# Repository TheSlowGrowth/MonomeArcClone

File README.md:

# Monome Arc Clone

An open source, protocol-compatible clone of the monome arc.

## Before you start

Please note: if you encounter a problem, please **do not post on the
monome forums**! Tehn will surely help you, but I don’t want my clone
to cause them trouble and work. I’m very happy that they make their
protocols open and I would like them to continue to do so in the spirit
of openness.

For assistance, please write an email to my address instead:
<mail@johannesneumann.net> I will try to help you out.

## Required tools

During assembly and setup you will need the following tools

-   AVR ISP programming device (supported by avrdude). I recommend
    [USBasp](http://www.fischl.de/usbasp/) or any of its clones.
    Alternatively you can also use STK500v2 clones or any other
    programmer that supports the ISP protocol. You get something like
    this on ebay for under 20€.
-   Soldering iron, decent(!) flux, tweezers, solder wick
-   a computer capable of flashing AVRs and FTDI EEPROMs
-   a multimeter

## Software installation

Before you start, please install all the software that’s needed to run monome devices. Please look at the instructions provided by [http://monome.org](http://monome.org/). Even though you might not have a functioning monome at this point, we will need the drivers during the setup process.

Install the drivers for your AVR ISP programmer, if you haven’t already.

### Windows

Install *WINAVR* from [this link](http://www.webring.org/l/rd?ring=avr;id=59;url=http://winavr.sourceforge.net/). This will install a AVR compiler and (more important) a tool called *avrdude* to upload the software to the ATMega88p microprocessor used in the device.

Install *AVR-Burn-O-Mat* from [this link](http://avr8-burn-o-mat.aaabbb.de/). This little tool will make it easier to upload the software to the chip as it provides a nice graphical user interface to *avrdude* installed with WINAVR.

Now we need to edit some files. Unfortunately as I am writing this (05.11.2014) it seems that some versions of *avrdude* and *AVR-Burn-O-Mat* don’t know the ATMega88p processor yet. So we teach them that it exists.

First, go to C:\\WINAVR\...\....\\bin\\avrdude.conf and open it with a text editor (I recommend geany).

Search for "ATMega88p". If it takes you to something like this:

```
#------------------------------------------------------------

# Atmega88p

#------------------------------------------------------------
```

…then you don’t have to edit anything and the file is fine. Simply go to the next step.

If nothing is found, search for this part:

```
#------------------------------------------------------------

# ATmega88

#------------------------------------------------------------
```

This is the header for the (almost) equal ATMega88. We simply copy the whole passage below this line (down to the next similar looking header) and change a few things. The whole passage you have to copy is roughly 200 lines long.

Duplicate the whole passage and change the beginning to:

```
#------------------------------------------------------------

# ATmega88p

#------------------------------------------------------------

part

id = "m88p";

desc = "ATMEGA88P";

has_debugwire = yes;

flash_instr = 0xB6, 0x01, 0x11;

eeprom_instr = 0xBD, 0xF2, 0xBD, 0xE1, 0xBB, 0xCF, 0xB4, 0x00,

0xBE, 0x01, 0xB6, 0x01, 0xBC, 0x00, 0xBB, 0xBF,

0x99, 0xF9, 0xBB, 0xAF;

stk500_devcode = 0x73;

# avr910_devcode = 0x;

signature = 0x1e 0x93 0x0f;

pagel = 0xd7;

bs2 = 0xc2;

...

... more stuff follows here ...

...
```

Now avrdude knows the microprocessor.

Now we have to teach *AVR-Burn-O-Mat* as well. Go to the installation directory (mine is: `D:\Program Files (x86)\AVR Burn-O-Mat)` and open the file `AVR8_Burn_O_Mat_Config.xml`. With a text editor (e.g. geany).

Again, search for "Atmega88p". If it can be found, all is well and you don't have to do anything here. If nothing is found, search for "Atmega88". It should take you to this line:

```
<AVR name="m88" caption="ATmega88">
   <Fuse name="UNUSED_E7" bit="7" ...

```
Copy the whole block (everything between `<AVR name="m88" ... ` and `</AVR>`) and change the first line to 
```
<AVR name="m88p" caption="ATmega88p">
```
Now *AVR-Burn-O-Mat* can program your Atmega88p processor.

Now open *AVR-Burn-O-Mat* and go to the settings page. Check if the directories are correct and enter the connection settings for your programmer.

I’m using an STK500V2 clone here, but if you click the dropdown menu, it will give you other options, such as USBasp. For most USB programmers, the Port must be set to "usb" or (if they are based on a serial COM interface) the respective COM port. You can open the device manager and plug in your programmer, then it should display the COM port in brackets behind the device name.

Install FT-Prog from [this website](http://www.ftdichip.com/Support/Utilities.htm). We will need it to configure the FTDI USB chip on the board.

### Linux

On Linux, install avrdude using your system’s package manager.

Compile libftdi with the confuse library already present, and make sure you can run the ftdi_eeprom command it comes with. This is currently untested on linux, please refer to [this guide](https://waterpigs.co.uk/articles/ftdi-configure-mac-linux/) for pointers on how to do it.

### Mac OS X

Install avrdude, and avr-gcc if you want to compile your own hex files. You can do this either manually, or via [CrossPack](https://obdev.at/products/crosspack/download.html).

In order to be able to flash the FTDI chip’s EEPROM, you’ll need to install libftdi with the confuse library already installed. This is possible either manually, or using homebrew with a change to the libftdi formula detailed [here](https://waterpigs.co.uk/articles/ftdi-configure-mac-linux/).

Some old versions of CrossPack will be missing the avrdude reference files for the ATMega88p. You can test this by running `avrdude -c stk500v2 -p m88p`. If you get `avrdude: AVR Part "88p" not found.` then follow the instructions in the Windows section above, duplicating the ATMega88 definition for the 88p. Look for an avrdude.conf file to make these changes in, e.g. `/usr/local/CrossPack-AVR-20100115/etc/avrdude.conf`

## USB Board Assembly

I won’t give step-by-step instructions for soldering. If you are not familiar with soldering and electronics in general, please do an easier project first. It can become very frustrating otherwise.

Once you’re done assembling the USB board, go to the device manager (Windows) or USB Prober (Mac OS). Connect the USB board to your computer via the USB jack and install the BUS\_PWRD jumper on the USB board. You should see the device manager refresh and a new COM port device will appear.

If it does not appear, please disconnect it immediately and check your soldering!

Now we have to check the voltage of the on-board regulator. Connect a multimeter to the pins highlighted in the following picture:

Your meter should read 3,6V (or thereabouts). Fine, it looks like everything is okay.

Lets go on and flash the firmware to the chip. Connect your programmer to the 10-pin connector on the USB board. This connector is not the one commonly used for AVR devices, but it uses the same pinout and attaches to the same type of cables. You can simply use your programmers 10-pin cable and crimp micromatch connector to it. This should now be plugged into the USB board. Check the orientation. A good help can be the four ground-pins, which are connected to each other. On both the USB board and the programmer. Pin 1 of the cable is on the opposite side. In the image above, it is the pin on the bottom right of the connector, next to the "R14" label.

Also be sure, that the USB board is plugged into your computer as well and the BUS\_PWRD jumper is installed, so the processor receives power.

### Windows (AVR-Burn-O-Mat + FT_PROG)

Open *AVR-Burn-O-Mat *and connect your programmer to your PC.

First, we need to change the fuse-bits in the processor, to use the external 20MHz crystal as a clock source. Select Atmega88p from the "AVR type" menu. Then click on "Fuses"

In the new window, click "read fuses".

You should see some commands run in the bottom of the main window and eventually a message will pop up, saying: "fuses successfully read". If not: Check the commands in the main window. They can give you a hint to where the problem is. Usually the programmer settings are wrong (wrong COM port\...) or the USB board is not connected properly. Some programmers offer a "low speed" programming mode, this should be used, as the processor is currently still running at its internal low clock speed.

If verything is fine, we can edit the fuse-bits to use the external crystal. Click on the "Oscillator/Clock Options" tab, then un-tick "divide system clock by 8" and select the "Full swing crystal oscillator" tab.

Double check everything! You might screw your chip up! Never attempt to write the fuses, if you were not able to correctly read them before. You might end up with a chip that has its programming interface disabled and can’t be rescued even with professional equipment.

Okay, once you are sure, everything is correct and matches the image below, you can click "write fuses" and again, some commands should run in the main window and a message should say: "Fuses successfully written". Then click "read fuses" again. If they can be read successfully, you have done everything right.

Now we can flash the firmware. Close the fuses window and select the firmware file in the main window. I recommend to use the pre-compiled one in the repository. I want to build an arc 4 here, so I chose the matching firmware. Be sure to use the right file. Using another file will probably make the processor "think" its connected to some hardware which is not there. This can create short circuits and might destroy the chip. So please double check here!

Click "write" and the commands in the bottom of the window should start executing again. Eventually it will say "Flash sucessfully written."

Nice! Now you can unplug the programmer.

Now we have to configure the USB-chip on the board to be recognized by serialosc so you can use your clone just like a real monome arc.

Start FT\_PROG and connect the USB board to your computer via its USB connector. In the FT\_PROG window, click the search icon until it displays your device.

Eventually after a few retries you get this. Go to the "SerialNumber" tab and untick "Auto Generate Serial No:". Now you can edit the "serial number" field. Enter a serial number like in the image above. It should start with an "m" and the numbers after that are irrelevant, but I found that they should be 7 digits long. They represent the "unique number" of your device. If you have other monomes, be sure that you use a different serial number that the one of your other devices. Also change the manufacturer to "monome", this is important for compatibility with monome eurorack modules and the Aleph. Once you’re done, click the flash symbol and program the new settings to the chip.

### Linux/Mac OS (avrdude + libftdi ftdi_eeprom)

Connect your AVR programmer to your computer, and the USB board to the programmer. In each of the following commands, replace `YOUR_PROGRAMMER_ID` with the relevant ID (e.g. stk500v2) and `YOUR_PROGRAMMER_PORT` with the relevant port (e.g. `/dev/cu.usbmodem00177932`.

First, set the fuses, based on [this fuse calculation](http://eleccelerator.com/fusecalc/fusecalc.php?chip=atmega88p&LOW=D6&HIGH=DF&EXTENDED=F9&LOCKBIT=FF):

`avrdude -V -p m88p -c YOUR_PROGRAMMER_ID -P YOUR_PROGRAMMER_PORT -B 10 -e -u -U lfuse:w:0xD6:m -U hfuse:w:0xDF:m -U efuse:w:0xF9:m -U lock:w:0xFF:m`

Then, flash the USB board firmware. Swap `arc4_` for `arc2_` in the unlikely event you’re building a two-ring arc:

`avrdude -V -p m88p -c YOUR_PROGRAMMER_ID -P YOUR_PROGRAMMER_PORT -B 2 -U flash:w:./firmware/compiled_hex/arc4_firmware_usb_board_atmega88p.hex:i -U lock:w:0xFF:m`

To flash the FTDI EEPROM, edit `firmware/monome-arc-clone-ftdi-eeprom.conf` to have your desired serial number (which must be m followed by seven digits), then run the following command with your FTDI driver disabled:

`ftdi_eeprom --flash-eeprom firmware/monome-arc-clone-ftdi-eeprom.conf`

Don’t forget to re-enable your FTDI driver afterwards! Refer to this [libftdi guide](https://waterpigs.co.uk/articles/ftdi-configure-mac-linux/) for more information.

### Testing

Now you can open a monome app with your USB board connected, and you should see your clone appear in the device list. If it does not appear, check your serialosc settings.

## Pot board and ring board assembly

Assemble the ring boards and the pot boards. Start with one pair of them to find errors early.

At full brightness, each LED is supplied with a 3.3V square wave with 25% duty cycle, current limited to around 2.6mA (with a 9.1kohm current set resistor). Not all LEDs perform well at such low currents. Testing found the IN-S63AT5UW to be an excellent trade-off between price and performance. Prices in the comparison are from late 2018.

When soldering the surface mounted headers which connect each ring board to the encoder board, solder only one connector first, insert the other connector onto that, then temporarily screw the boards together and make a couple of solder joints to fix the other connector in exactly the right mating position. If soldered without checking the location, you risk the boards being misaligned.

Use the 8pin micromatch connectors and ribbon cables to connect the pot board to the USB board via their micromatch connectors (Not the one marked with ISP, the smaller one.) Connect the USB board to your computer and check the BUS\_PWRD jumper. The USB board should now receive power, and supply the pot board via the ribbon cable that connects the two.

Attach your AVR programmer to the board, then set the fuses and flash the firmware as with the USB Board, but using `firmware_pot_board_atmega88p.hex` rather than the USB board hex file.

Once the pot boards processor is programmed with the right fuses and firmware, you should disconnect the usb cable and set the address selection switch to off/off. This equals to address 0, which is used for the first LED ring in the monome arc clone.

Now attach the led ring.

Connect the USB board to the computer again and the led ring should light up for a short time (part of the startup animation). Open the [monome arc test app](http://docs.monome.org/lib/exe/fetch.php?media=app:monome_test_110.zip) and check everything.

Then assemble the other boards and connect them to the ribbon cable. Flash them the same way and check them with the test app. Be sure to use the right addresses:

```
  ------------- ---------- ----------
  Ring number   Switch 2   Switch 1
  0             Off        Off
  1             Off        On
  2             On         Off
  3             On         On
  ------------- ---------- ----------
```

Double check that all the boards function correctly before final assembly. Make sure that all LEDs light, that the encoders send turn and button press messages, and that the boards are in the right order.

If you don’t have Max MSP and don’t want to install the very large free Max player, you can use the small Puredata arc test patch in `firmware/arc-scratchpad.pd` to test and debug your arc. It should run in any version of Puredata, and requires no externals.

## Physical Case Construction and Assembly

Assuming you’re working with a milled panel based on `case/Alu Faceplate.pdf` and laser cut acrylic parts based on the Glas-Ring and Light_Shaper drawings, assembly is quite straightforward. The fit of the laser cut parts is tight, and often the outer diameter is slightly larger on one edge than the other, so look carefully at the edge angles of both parts and experiment with their orientation to find the best results. You can see the angles here:

Depending on the quality of your laser cutter, you may have to manually remove some leftover parts from the light shaper with a small sharp knife.

For a more diffused light from the LEDs, either cut the rings from frosted acyrlic, lightly sand the underside of the rings with 400 grit sandpaper, or perhaps put a ring of very thin paper between the ring and light shaper.

The blind threaded holes in the top panel are not deep enough for normal male-female M3 hex spacers, so insert 12mm setscrews (preferably fastened with thread lock e.g. loctite) and then screw 4mm female-female hex spacers over them before attaching the ring board.

The simplest case solution is to cut a 4mm acrylic backplate from `case/Acrylic Glass Back Panel 266 x 74.svg`, then assemble the boards and plates as shown (note that the given acrylic back plate has one set of mounting holes in a different location to shown here. Either cut the backplate with holes in the outside corners, or alter the assembly to suit):

You’ll need the following hardware:

* 16 x 12mm M3 Set Screw
* 16 x 4mm M3 FF hex spacer
* 10 x 12mm M3 FF hex spacer
* 4 x 4mm M3 MF hex spacer
* 6 x M3 Nut
* 6 x 6mm M3 Screw
* 4 x 8mm M3 Screw

If you want to build a more comprehensive case, refer to the layout in `case/Monome Arc Clone Walnut Case.ezdraw` and `case/Monome Arc Clone Walnut Case Plans 500 x 360.svg` for dimensions to design a case around. Make sure the bounding box in the SVG is scaled to 500mm by 360mm in your CAD application, and then everything else should be the correct size. Parts for the CNC-routed wooden case and knobs shown below are given as an example.

Congratulations on assembling your arc!

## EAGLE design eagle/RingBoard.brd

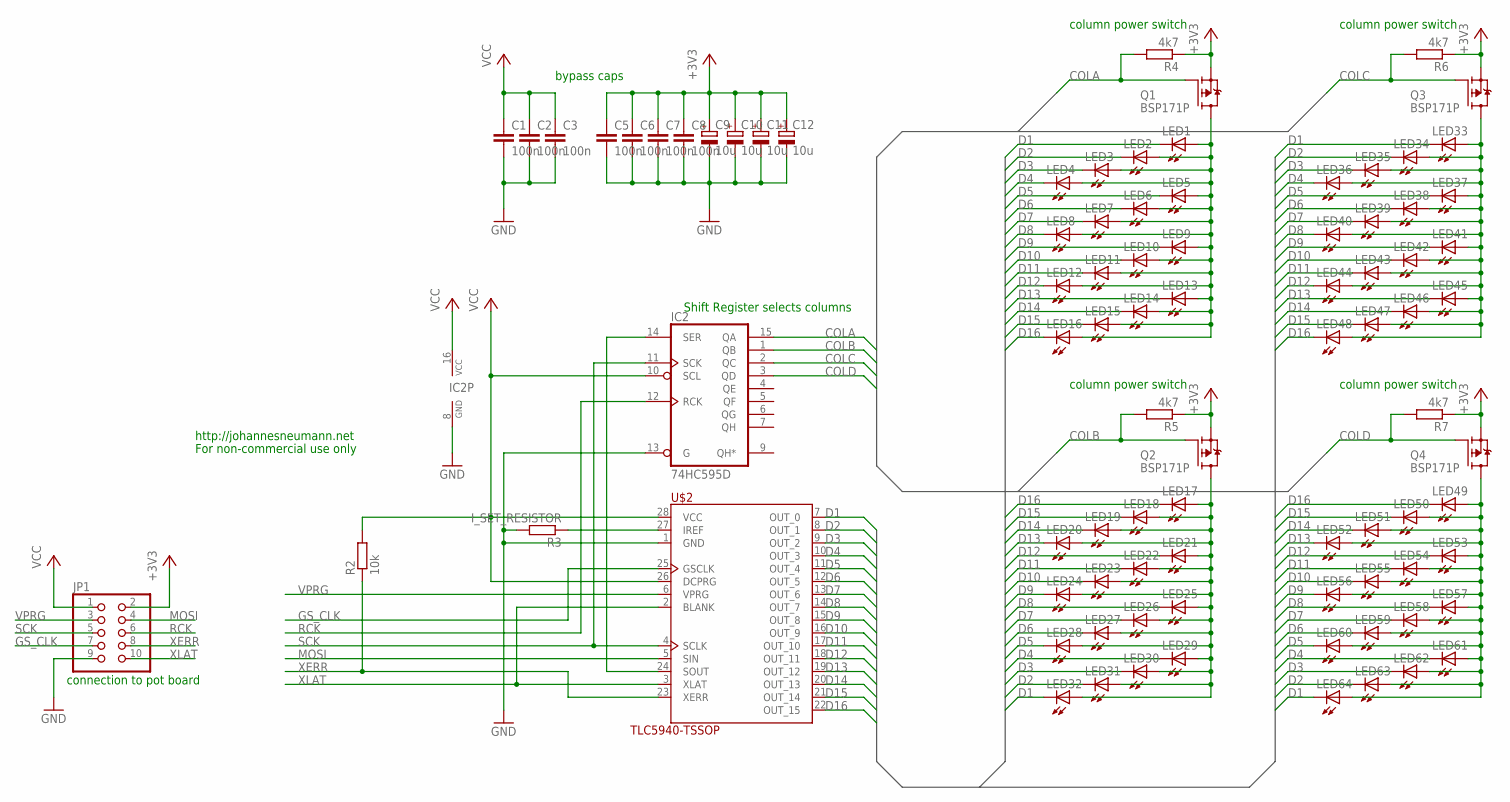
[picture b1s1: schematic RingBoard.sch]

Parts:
C1, C2, C3, C5, C6, C7, C8: 100n; C0603
C9, C10, C11, C12: 10u; 153CLV-0605
IC2: 74HC595D; SO16
JP1: PINHD-2X5_2.54-SMD; 2X05SMD
LED1, LED2, LED3, LED4, LED5, LED6, LED7, LED8, LED9, LED10, LED11, LED12, LED13, LED14, LED15, LED16, LED17, LED18, LED19, LED20, LED21, LED22, LED23, LED24, LED25, LED26, LED27, LED28, LED29, LED30, LED31, LED32, LED33, LED34, LED35, LED36, LED37, LED38, LED39, LED40, LED41, LED42, LED43, LED44, LED45, LED46, LED47, LED48, LED49, LED50, LED51, LED52, LED53, LED54, LED55, LED56, LED57, LED58, LED59, LED60, LED61, LED62, LED63, LED64: LEDCHIP-LED0805; CHIP-LED0805
Q1, Q2, Q3, Q4: BSP171P; SOT223
R2: 10k; R0603
R3: I_SET_RESISTOR; M1406
R4, R5, R6, R7: 4k7; R0603
U$2: TLC5940-TSSOP; HTSSOP-28

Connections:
+3V3: C5.1, C6.1, C7.1, C8.1, C9.+, C10.+, C11.+, C12.+, JP1.2, Q1.3 (S), Q2.3 (S), Q3.3 (S), Q4.3 (S), R4.1, R5.1, R6.1, R7.1
COLA: IC2.15 (QA), Q1.1 (G), R4.2
COLB: IC2.1 (QB), Q2.1 (G), R5.2
COLC: IC2.2 (QC), Q3.1 (G), R6.2
COLD: IC2.3 (QD), Q4.1 (G), R7.2
D1: LED1.C, LED32.C, LED33.C, LED64.C, U$2.7 (OUT_0)
D2: LED2.C, LED31.C, LED34.C, LED63.C, U$2.8 (OUT_1)
D3: LED3.C, LED30.C, LED35.C, LED62.C, U$2.9 (OUT_2)
D4: LED4.C, LED29.C, LED36.C, LED61.C, U$2.10 (OUT_3)
D5: LED5.C, LED28.C, LED37.C, LED60.C, U$2.11 (OUT_4)
D6: LED6.C, LED27.C, LED38.C, LED59.C, U$2.12 (OUT_5)
D7: LED7.C, LED26.C, LED39.C, LED58.C, U$2.13 (OUT_6)
D8: LED8.C, LED25.C, LED40.C, LED57.C, U$2.14 (OUT_7)
D9: LED9.C, LED24.C, LED41.C, LED56.C, U$2.15 (OUT_8)
D10: LED10.C, LED23.C, LED42.C, LED55.C, U$2.16 (OUT_9)
D11: LED11.C, LED22.C, LED43.C, LED54.C, U$2.17 (OUT_10)
D12: LED12.C, LED21.C, LED44.C, LED53.C, U$2.18 (OUT_11)
D13: LED13.C, LED20.C, LED45.C, LED52.C, U$2.19 (OUT_12)
D14: LED14.C, LED19.C, LED46.C, LED51.C, U$2.20 (OUT_13)
D15: LED15.C, LED18.C, LED47.C, LED50.C, U$2.21 (OUT_14)
D16: LED16.C, LED17.C, LED48.C, LED49.C, U$2.22 (OUT_15)
GND: C1.2, C2.2, C3.2, C5.2, C6.2, C7.2, C8.2, C9.-, C10.-, C11.-, C12.-, IC2.8 (GND), IC2.13 (G), JP1.9, R3.2, U$2.1 (GND)
GS_CLK: JP1.7, U$2.25 (GSCLK)
MOSI: JP1.4, U$2.5 (SIN)
unnamed: IC2.14 (SER), U$2.24 (SOUT)
unnamed: LED17.A, LED18.A, LED19.A, LED20.A, LED21.A, LED22.A, LED23.A, LED24.A, LED25.A, LED26.A, LED27.A, LED28.A, LED29.A, LED30.A, LED31.A, LED32.A, Q2.2 (D), Q2.4 (D)
unnamed: LED33.A, LED34.A, LED35.A, LED36.A, LED37.A, LED38.A, LED39.A, LED40.A, LED41.A, LED42.A, LED43.A, LED44.A, LED45.A, LED46.A, LED47.A, LED48.A, Q3.2 (D), Q3.4 (D)
unnamed: LED49.A, LED50.A, LED51.A, LED52.A, LED53.A, LED54.A, LED55.A, LED56.A, LED57.A, LED58.A, LED59.A, LED60.A, LED61.A, LED62.A, LED63.A, LED64.A, Q4.2 (D), Q4.4 (D)
unnamed: LED1.A, LED2.A, LED3.A, LED4.A, LED5.A, LED6.A, LED7.A, LED8.A, LED9.A, LED10.A, LED11.A, LED12.A, LED13.A, LED14.A, LED15.A, LED16.A, Q1.2 (D), Q1.4 (D)
unnamed: R3.1, U$2.27 (IREF)
RCK: IC2.12 (RCK), JP1.6
SCK: IC2.11 (SCK), JP1.5, U$2.4 (SCLK)
VCC: C1.1, C2.1, C3.1, IC2.10 (SCL), IC2.16 (VCC), JP1.1, R2.2, U$2.26 (DCPRG), U$2.28 (VCC)
VPRG: JP1.3, U$2.6 (VPRG)
XERR: JP1.8, R2.1, U$2.23 (XERR)
XLAT: JP1.10, U$2.2 (BLANK), U$2.3 (XLAT)

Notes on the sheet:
Shift Register selects columns
http://johannesneumann.net
For non-commercial use only
connection to pot board
column power switch
bypass caps

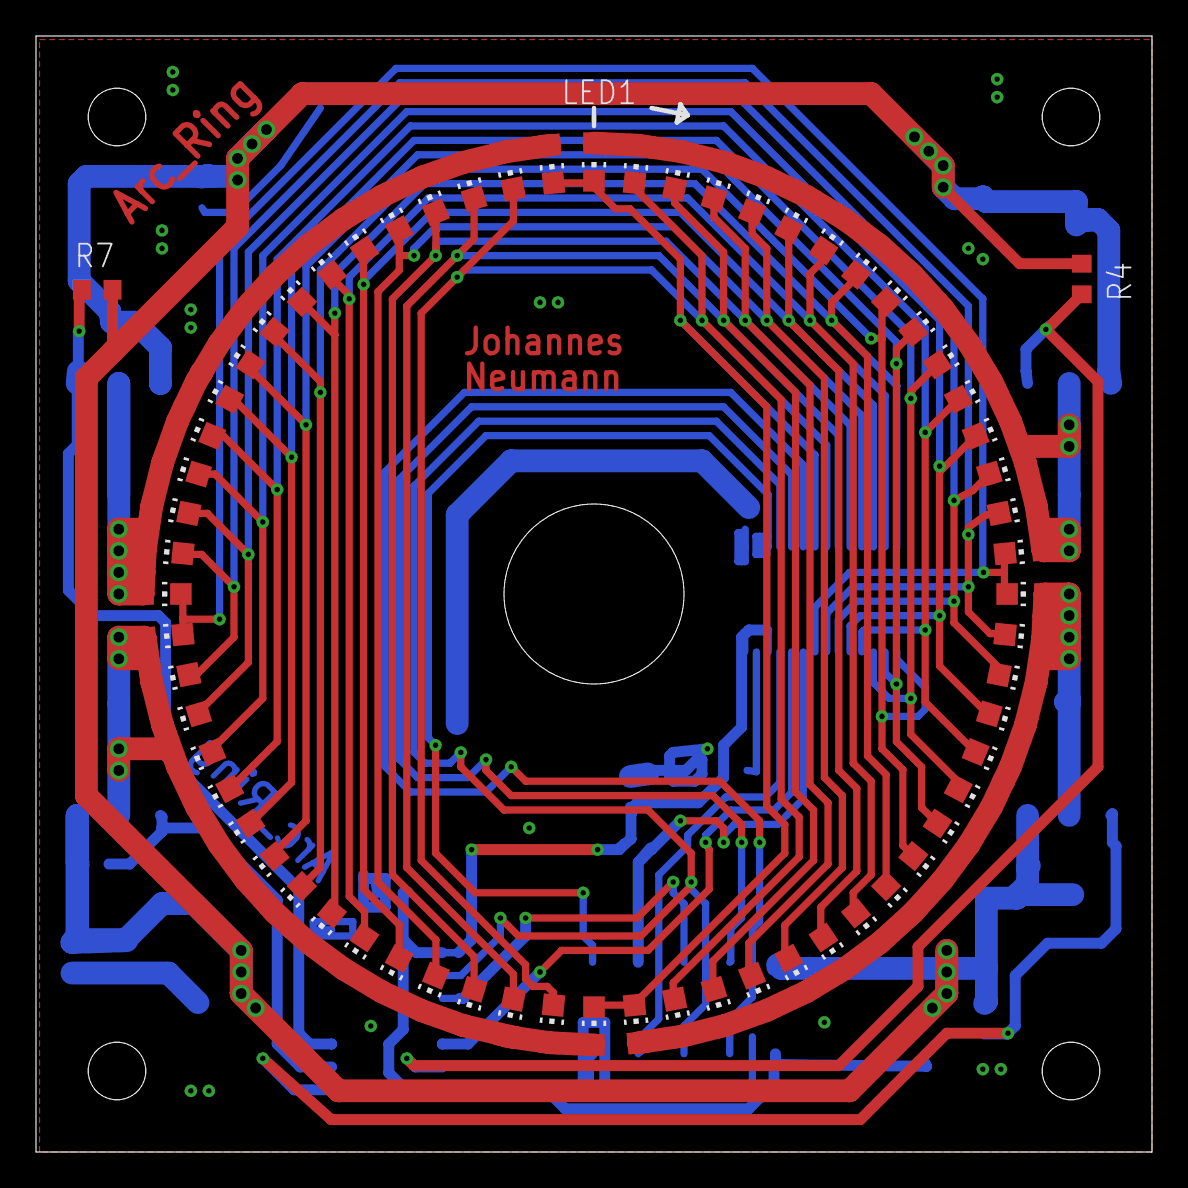
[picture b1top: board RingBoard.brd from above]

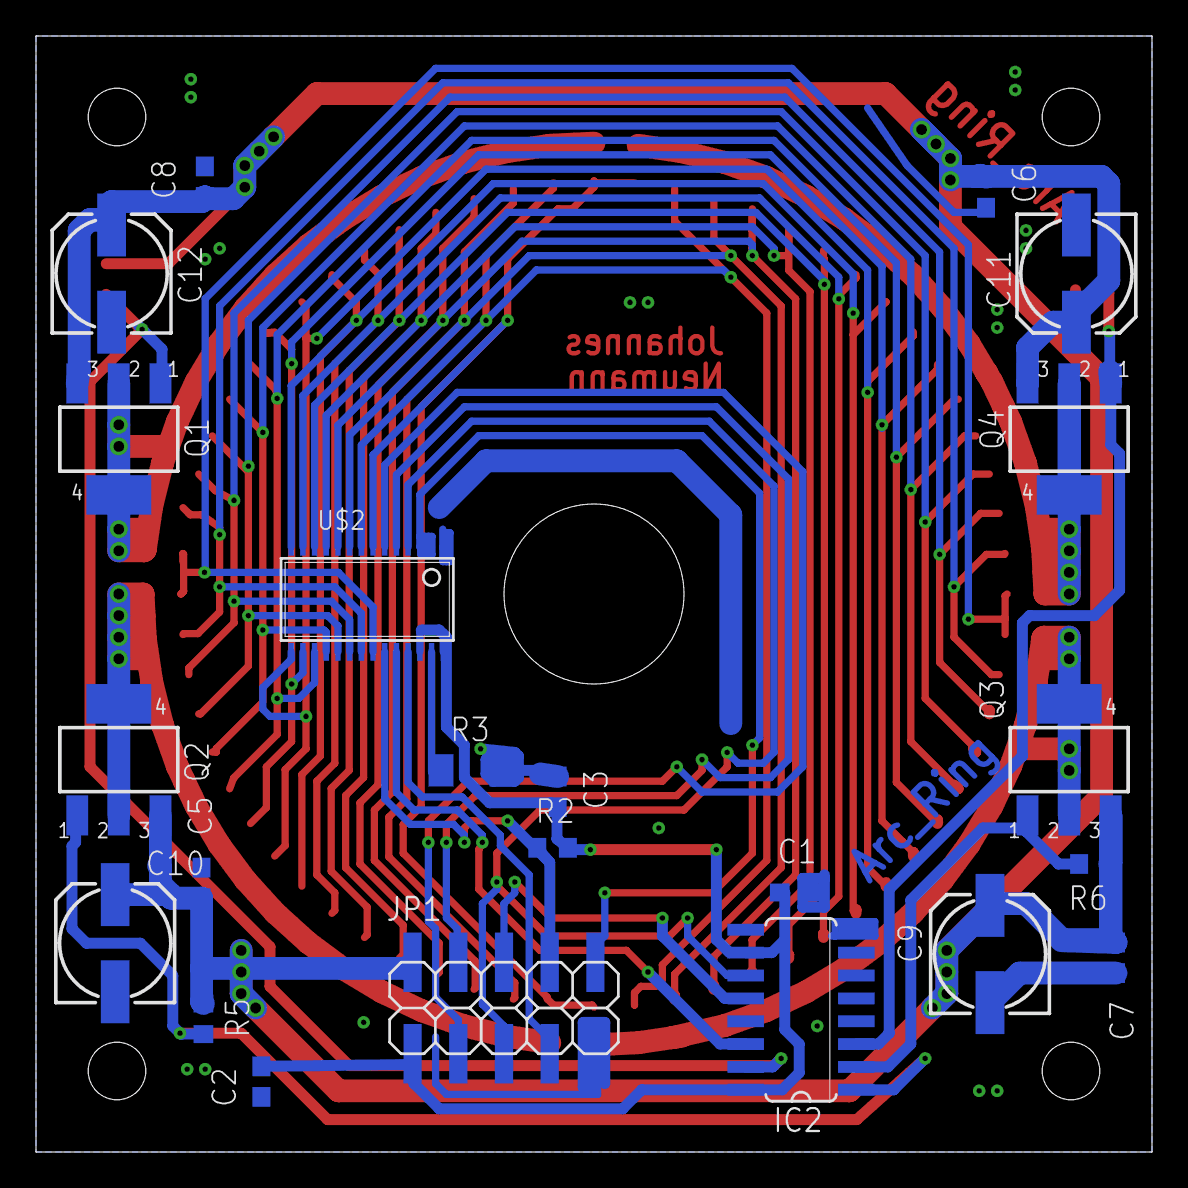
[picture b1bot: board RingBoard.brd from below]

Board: 2 copper layers, 62.0 x 62.0 mm, 88 parts (22 on the bottom side), 36 nets.

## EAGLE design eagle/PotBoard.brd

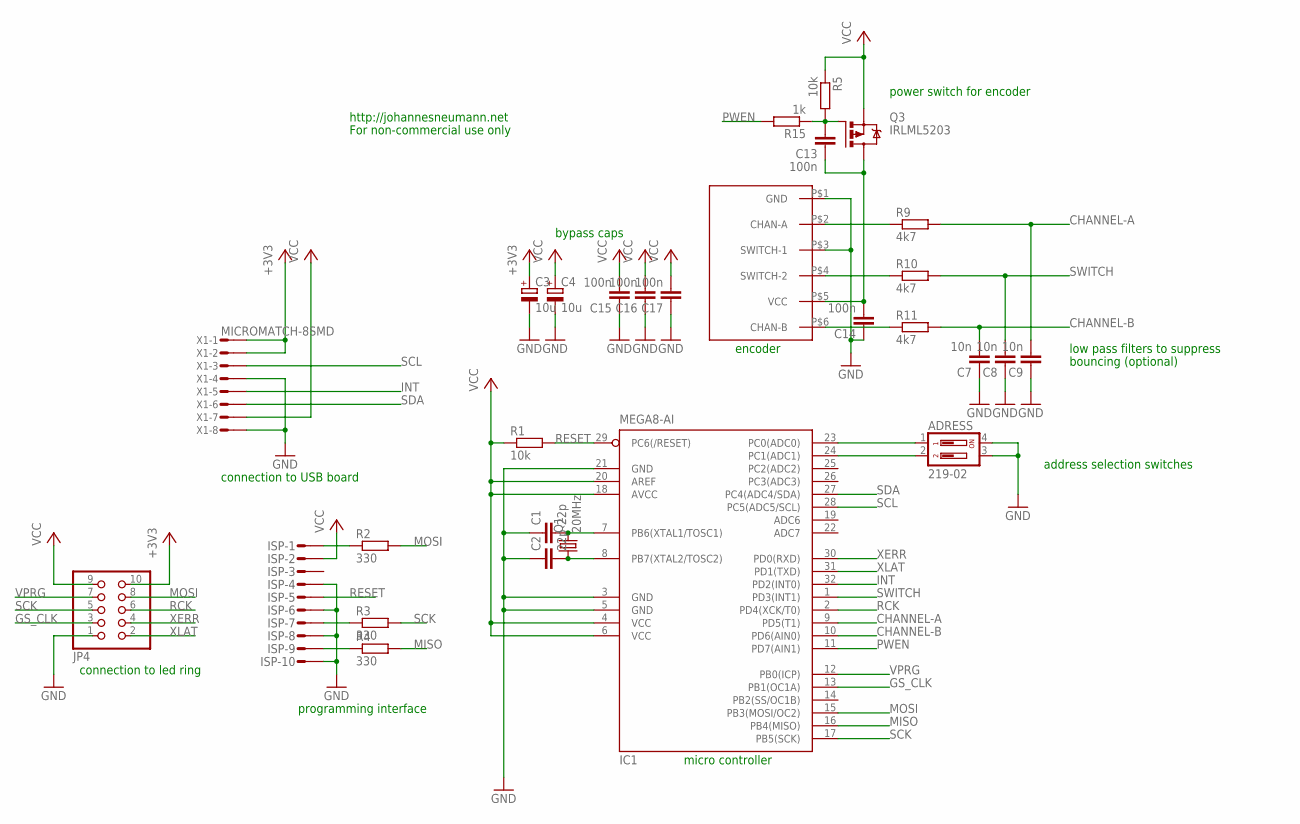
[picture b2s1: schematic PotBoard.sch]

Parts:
ADRESS: 219-02; CTS-219-02
C1, C2: 22p; C0603
C3, C4: 10u; 153CLV-0505
C7, C8, C9: 10n; C0603
C13, C14, C15, C16, C17: 100n; C0603
IC1: MEGA8-AI; TQFP32-08
ISP: MICROMATCH-10-SMD
JP4: PINHD-2X5_2.54-SMD; 2X05SMD
Q1: 20MHz; SM49
Q3: IRLML5203; MICRO3
R1, R5: 10k; R0603
R2, R3, R4: 330; R0603
R9, R10, R11: 4k7; R0603
R15: 1k; R0603
U$1: BOURNS_EM14; BOURNS_EM14_AXIAL
X1: MICROMATCH-8SMD; MICROMATCH-8-SMD

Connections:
+3V3: C3.+, JP4.10, X1.1, X1.2
CHANNEL-A: C9.2, IC1.9 (PD5(T1)), R9.2
CHANNEL-B: C7.2, IC1.10 (PD6(AIN0)), R11.2
GND: ADRESS.3, ADRESS.4, C1.1, C2.1, C3.-, C4.-, C7.1, C8.1, C9.1, C14.1, C15.1, C16.1, C17.1, IC1.3 (GND), IC1.5 (GND), IC1.21 (GND), ISP.P$4, ISP.P$6, ISP.P$8, ISP.P$10, JP4.1, U$1.P$1 (GND), U$1.P$3 (SWITCH-1), X1.4, X1.8
GS_CLK: IC1.13 (PB1(OC1A)), JP4.3
INT: IC1.32 (PD2(INT0)), X1.5
MISO: IC1.16 (PB4(MISO)), R4.2
MOSI: IC1.15 (PB3(MOSI/OC2)), JP4.8, R2.2
unnamed: C1.2, IC1.7 (PB6(XTAL1/TOSC1)), Q1.2
unnamed: C2.2, IC1.8 (PB7(XTAL2/TOSC2)), Q1.1
unnamed: ISP.P$1, R2.1
unnamed: ISP.P$7, R3.1
unnamed: ISP.P$9, R4.1
unnamed: ADRESS.1, IC1.23 (PC0(ADC0))
unnamed: ADRESS.2, IC1.24 (PC1(ADC1))
unnamed: R11.1, U$1.P$6 (CHAN-B)
unnamed: R10.1, U$1.P$4 (SWITCH-2)
unnamed: R9.1, U$1.P$2 (CHAN-A)
unnamed: C13.2, Q3.1 (G), R5.2, R15.1
unnamed: C13.1, C14.2, Q3.3 (D), U$1.P$5 (VCC)
PWEN: IC1.11 (PD7(AIN1)), R15.2
RCK: IC1.2 (PD4(XCK/T0)), JP4.6
RESET: IC1.29 (PC6(/RESET)), ISP.P$5, R1.2
SCK: IC1.17 (PB5(SCK)), JP4.5, R3.2
SCL: IC1.28 (PC5(ADC5/SCL)), X1.3
SDA: IC1.27 (PC4(ADC4/SDA)), X1.6
SWITCH: C8.2, IC1.1 (PD3(INT1)), R10.2
VCC: C4.+, C15.2, C16.2, C17.2, IC1.4 (VCC), IC1.6 (VCC), IC1.18 (AVCC), IC1.20 (AREF), ISP.P$2, JP4.9, Q3.2 (S), R1.1, R5.1, X1.7
VPRG: IC1.12 (PB0(ICP)), JP4.7
XERR: IC1.30 (PD0(RXD)), JP4.4
XLAT: IC1.31 (PD1(TXD)), JP4.2

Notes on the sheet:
http://johannesneumann.net
For non-commercial use only
power switch for encoder
encoder
low pass filters to suppress
bouncing (optional)
address selection switches
connection to led ring
programming interface
connection to USB board
bypass caps
micro controller

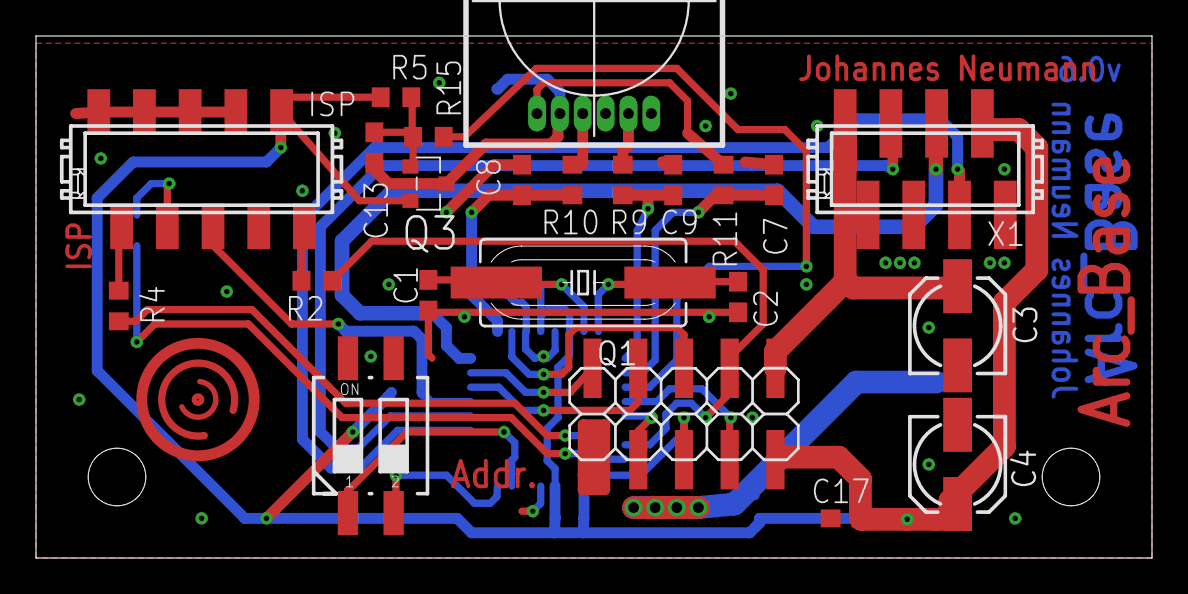
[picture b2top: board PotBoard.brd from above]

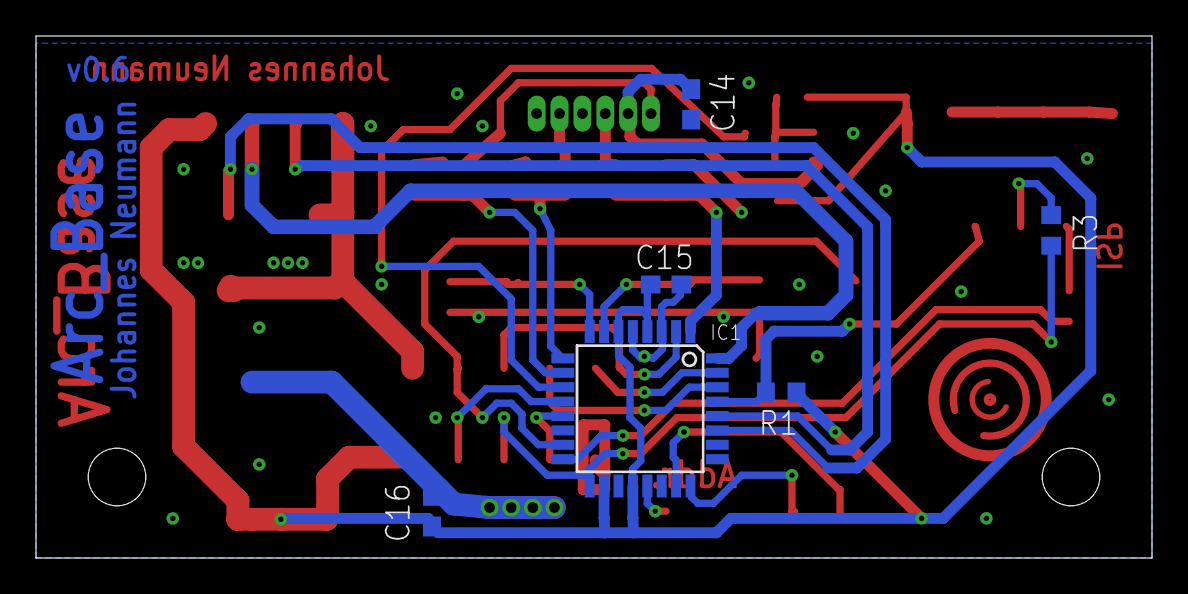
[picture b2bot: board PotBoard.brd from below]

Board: 2 copper layers, 62.0 x 29.0 mm, 29 parts (6 on the bottom side), 31 nets.

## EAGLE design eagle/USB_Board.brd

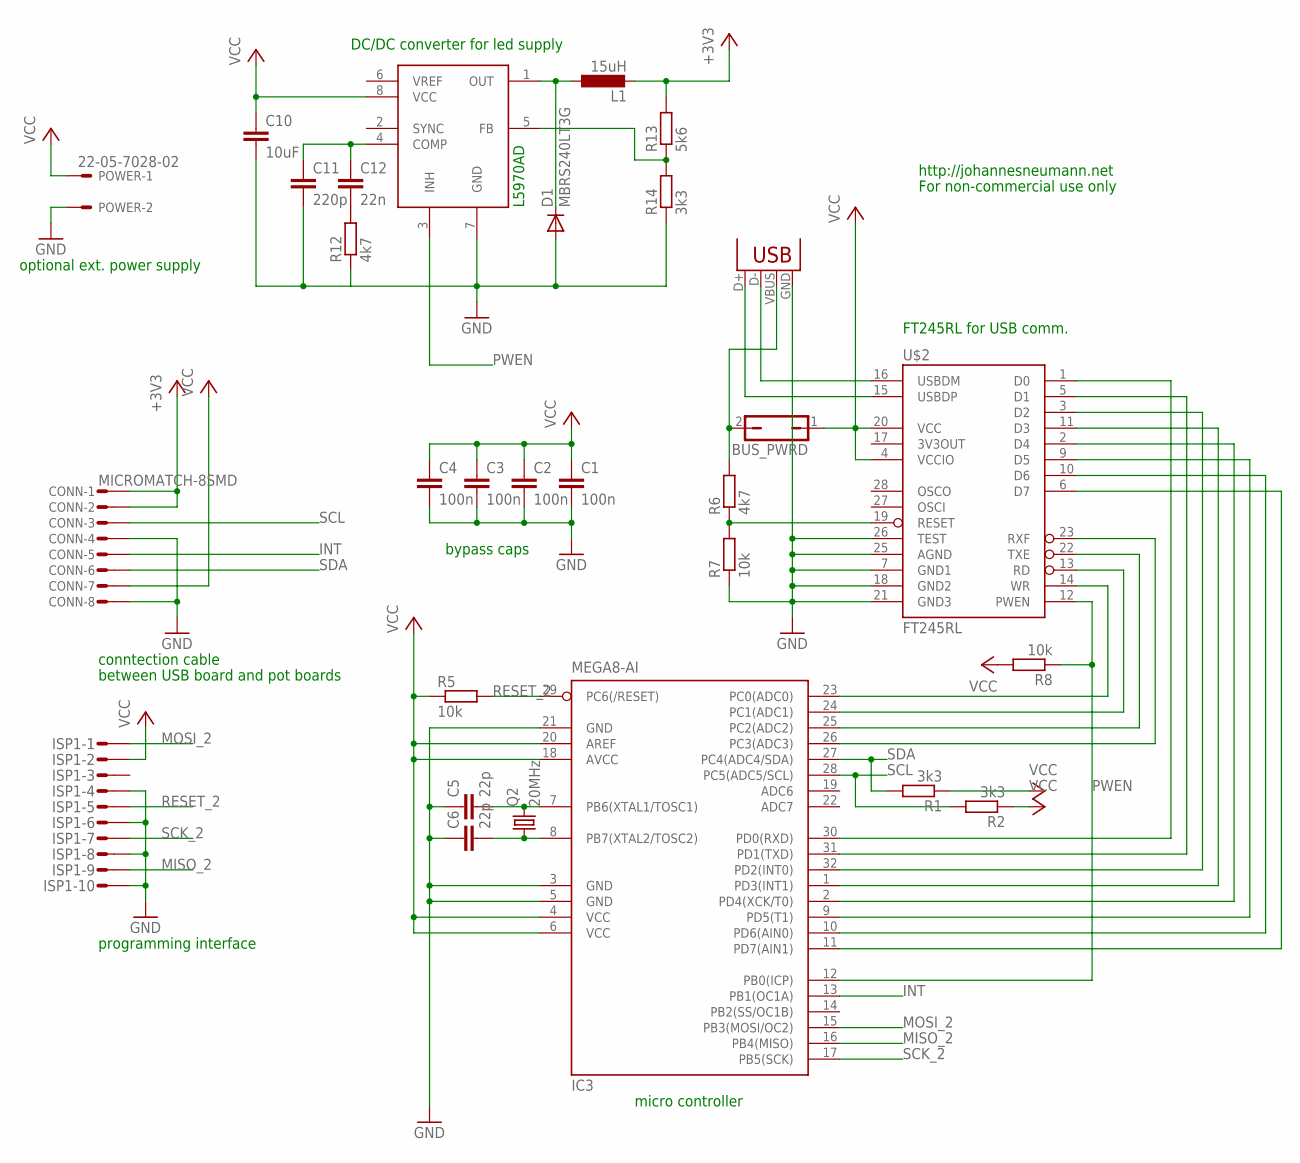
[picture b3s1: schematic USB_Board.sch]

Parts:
BUS_PWRD: JP1Q; JP1
C1, C2, C3, C4: 100n; C0603
C5, C6: 22p; C0603
C10: 10uF; C0805
C11: 220p; C0603
C12: 22n; C0603
CONN: MICROMATCH-8SMD; MICROMATCH-8-SMD
D1: MBRS240LT3G; DO41-10
IC3: MEGA8-AI; TQFP32-08
ISP1: MICROMATCH-10-SMD
L1: 15uH; PIS2816
POWER: 22-05-7028-02; 7395-02
Q2: 20MHz; SM49
R1, R2, R14: 3k3; R0603
R5, R7, R8: 10k; R0603
R6, R12: 4k7; R0603
R13: 5k6; R0603
U$2: FT245RL; SSOP28DB
U$3: L5970AD; SO8
X1: USBPTH; USB-B-PTH

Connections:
+3V3: CONN.1, CONN.2, L1.2, R13.2
GND: C1.2, C2.2, C3.2, C4.2, C5.1, C6.1, C10.2, C11.2, CONN.4, CONN.8, D1.A, IC3.3 (GND), IC3.5 (GND), IC3.21 (GND), ISP1.P$4, ISP1.P$6, ISP1.P$8, ISP1.P$10, POWER.2, R7.1, R12.1, R14.1, U$2.7 (GND1), U$2.18 (GND2), U$2.21 (GND3), U$2.25 (AGND), U$2.26 (TEST), U$3.7 (GND), X1.GND
INT: CONN.5, IC3.13 (PB1(OC1A))
MISO_2: IC3.16 (PB4(MISO)), ISP1.P$9
MOSI_2: IC3.15 (PB3(MOSI/OC2)), ISP1.P$1
unnamed: C5.2, IC3.7 (PB6(XTAL1/TOSC1)), Q2.2
unnamed: C6.2, IC3.8 (PB7(XTAL2/TOSC2)), Q2.1
unnamed: U$2.16 (USBDM), X1.D-
unnamed: IC3.30 (PD0(RXD)), U$2.1 (D0)
unnamed: IC3.31 (PD1(TXD)), U$2.5 (D1)
unnamed: IC3.32 (PD2(INT0)), U$2.3 (D2)
unnamed: IC3.1 (PD3(INT1)), U$2.11 (D3)
unnamed: IC3.2 (PD4(XCK/T0)), U$2.2 (D4)
unnamed: IC3.9 (PD5(T1)), U$2.9 (D5)
unnamed: IC3.10 (PD6(AIN0)), U$2.10 (D6)
unnamed: IC3.11 (PD7(AIN1)), U$2.6 (D7)
unnamed: IC3.26 (PC3(ADC3)), U$2.23 (RXF)
unnamed: IC3.25 (PC2(ADC2)), U$2.22 (TXE)
unnamed: IC3.24 (PC1(ADC1)), U$2.13 (RD)
unnamed: IC3.23 (PC0(ADC0)), U$2.14 (WR)
unnamed: D1.C, L1.1, U$3.1 (OUT)
unnamed: BUS_PWRD.2, R6.2, X1.VBUS
unnamed: R13.1, R14.2, U$3.5 (FB)
unnamed: C12.2, R12.2
unnamed: C11.1, C12.1, U$3.4 (COMP)
PWEN: IC3.12 (PB0(ICP)), R8.1, U$2.12 (PWEN), U$3.3 (INH)
PWR_ON: R6.1, R7.2, U$2.19 (RESET)
RESET_2: IC3.29 (PC6(/RESET)), ISP1.P$5, R5.2
SCK_2: IC3.17 (PB5(SCK)), ISP1.P$7
SCL: CONN.3, IC3.28 (PC5(ADC5/SCL)), R2.2
SDA: CONN.6, IC3.27 (PC4(ADC4/SDA)), R1.2
USB: U$2.15 (USBDP), X1.D+
VCC: BUS_PWRD.1, C1.1, C2.1, C3.1, C4.1, C10.1, CONN.7, IC3.4 (VCC), IC3.6 (VCC), IC3.18 (AVCC), IC3.20 (AREF), ISP1.P$2, POWER.1, R1.1, R2.1, R5.1, R8.2, U$2.4 (VCCIO), U$2.20 (VCC), U$3.8 (VCC)

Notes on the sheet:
programming interface
conntection cable
between USB board and pot boards
optional ext. power supply
DC/DC converter for led supply
FT245RL for USB comm.
micro controller
bypass caps
http://johannesneumann.net
For non-commercial use only
L5970AD

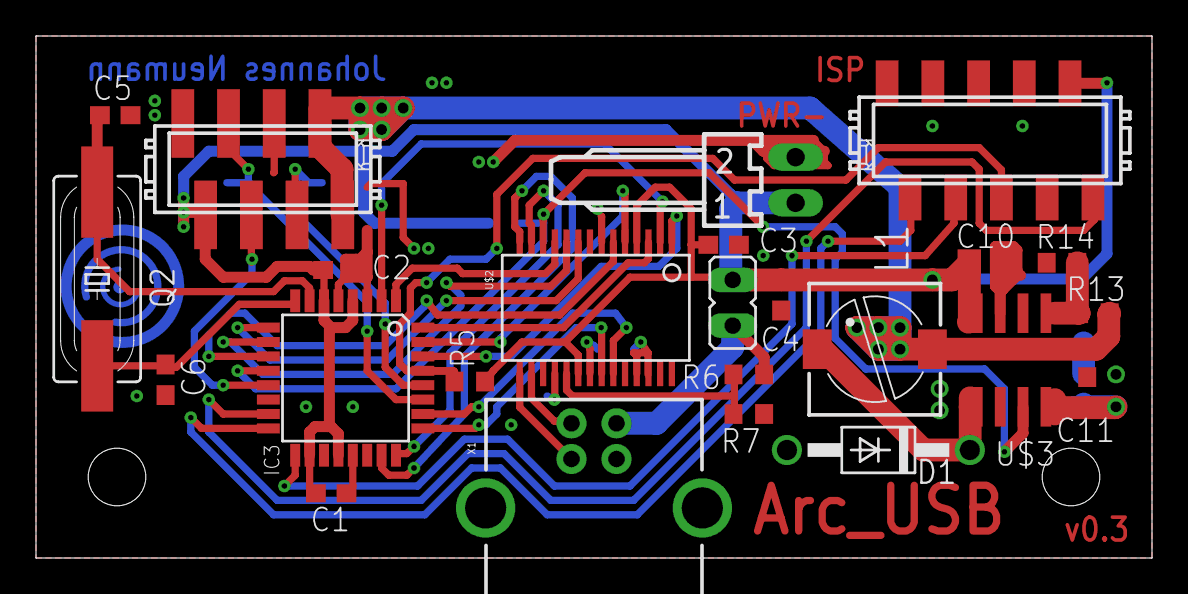
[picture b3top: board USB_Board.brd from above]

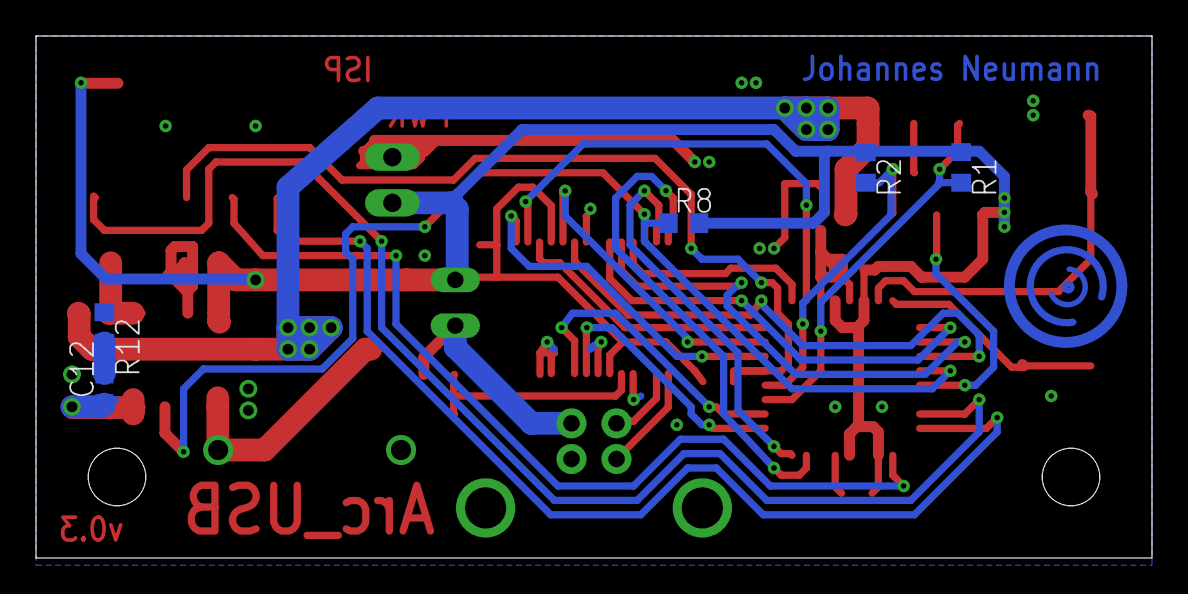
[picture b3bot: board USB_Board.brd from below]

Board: 2 copper layers, 62.0 x 29.0 mm, 29 parts (5 on the bottom side), 33 nets.

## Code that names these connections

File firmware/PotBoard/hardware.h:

/*	 This file contains source code for the firmware of a monome arc 
 *   clone.
 * 
 *   Copyright (C) 2013  Johannes Neumann; mail@johannesneumann.net
 *
 *   This program is free software: you can redistribute it and/or modify
 *   it under the terms of the GNU General Public License as published by
 *   the Free Software Foundation, either version 3 of the License, or
 *   (at your option) any later version.
 *
 *   This program is distributed in the hope that it will be useful,
 *   but WITHOUT ANY WARRANTY; without even the implied warranty of
 *   MERCHANTABILITY or FITNESS FOR A PARTICULAR PURPOSE.  See the
 *   GNU General Public License for more details.
 *
 *   You should have received a copy of the GNU General Public License
 *   along with this program.  If not, see <http://www.gnu.org/licenses/>.
 */  
 
/*********************************************************
 * This file holds defines for hardware configuration
 * 
 * Using these in the code makes it much more readable.
 ********************************************************/

// Defines for the TLC5940
#define OUT_XLAT 	DDRD |= (1<<PD1)
#define XLAT_HIGH 	PORTD |= (1<<PD1)
#define XLAT_LOW 	PORTD &= ~(1<<PD1)

#define OUT_VPRG 	DDRB |= (1<<PB0)
#define VPRG_HIGH 	PORTB |= (1<<PB0)
#define VPRG_LOW 	PORTB &= ~(1<<PB0)

#define OUT_GSCLK	DDRB |= (1<<PB1)
#define GSCLK_HIGH 	PORTB |= (1<<PB1)
#define GSCLK_LOW 	PORTB &= ~(1<<PB1)

#define XERR_HIGH 	bit_is_set(PIND, PD0)

// Defines for the 74HC595
#define OUT_RCK 	DDRD |= (1<<PD4)
#define RCK_HIGH 	PORTD |= (1<<PD4)
#define RCK_LOW 	PORTD &= ~(1<<PD4)


// Defines for the communication port
#define INT_LOW 		PORTD &= ~(1<<PD2); DDRD |= (1<<PD2);
#define INT_RELEASE 	DDRD &= ~(1<<PD2);
#define INT_IS_HIGH 	bit_is_set(PIND, PD2)

// Defines for the adress switch
#define ADDR_SW_PULLUPS	PORTC |= (1<<PC0) | (1<<PC1) | (1<<PC2) | (1<<PC3)
#define ADRR			~(PINC | 0xF0) + 1


// Defines for the rotary encoder
#define ENC_SWITCH_PULLUP   PORTD |= (1<<PD3)
#define ENC_POWER_OUTPUT   	DDRD |= (1<<PD7)
#define ENC_POWER_OFF   	PORTD |= (1<<PD7)
#define ENC_POWER_ON	  	PORTD &= ~(1<<PD7)
#define ENC_SWITCH_IS_HIGH 	bit_is_set(PIND, PD3)
#define ENC_CHAN_A_IS_HIGH 	bit_is_set(PIND, PD5)
#define ENC_CHAN_B_IS_HIGH 	bit_is_set(PIND, PD6)

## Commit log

2014-10-25 fixed makefile and included precompiled hex files for convenience
2014-11-05 Removed a stupid error from the pcbs and included an instructions file. Switched the firmware to use just two switches instead of four. No one's gonna build an arc16 anyway.
2014-11-05 instructions file fixed
2014-11-07 BOM fix
2015-07-28 Added license
2016-05-26 Update license.txt
    edited license
2016-10-28 Compatibility with ansible and other monome/libavr32 based hosts
2018-11-27 possible fix for friendly_name not reported correctly by serialosc
2018-11-28 removed some compiler warnings, remvoed trailing spaces from ID string (not allowed according to monome documentation)
2018-11-28 Added FPD designer file, CSV BOMs for each board
2018-11-28 Changed device ID to match original monome IDs
2019-02-27 Layer visibility change
2019-02-28 Updated BOM and documentation
    * Moved the assembly instructions to README.md
    * Added more detail and cross-platform instructions to many steps
    * Added section on physical assembly and case construction
    * Added design files detailing layout and suggested wooden case construction
2019-02-28 Corrected photo URL
2019-02-28 Small typographical fixes
2019-02-28 More small typographical fixes
2019-02-28 Added puredata debugging and test patch
2019-02-28 Update README.md
    fixed some lines that went mising in BarnabyWalters documentation changes
